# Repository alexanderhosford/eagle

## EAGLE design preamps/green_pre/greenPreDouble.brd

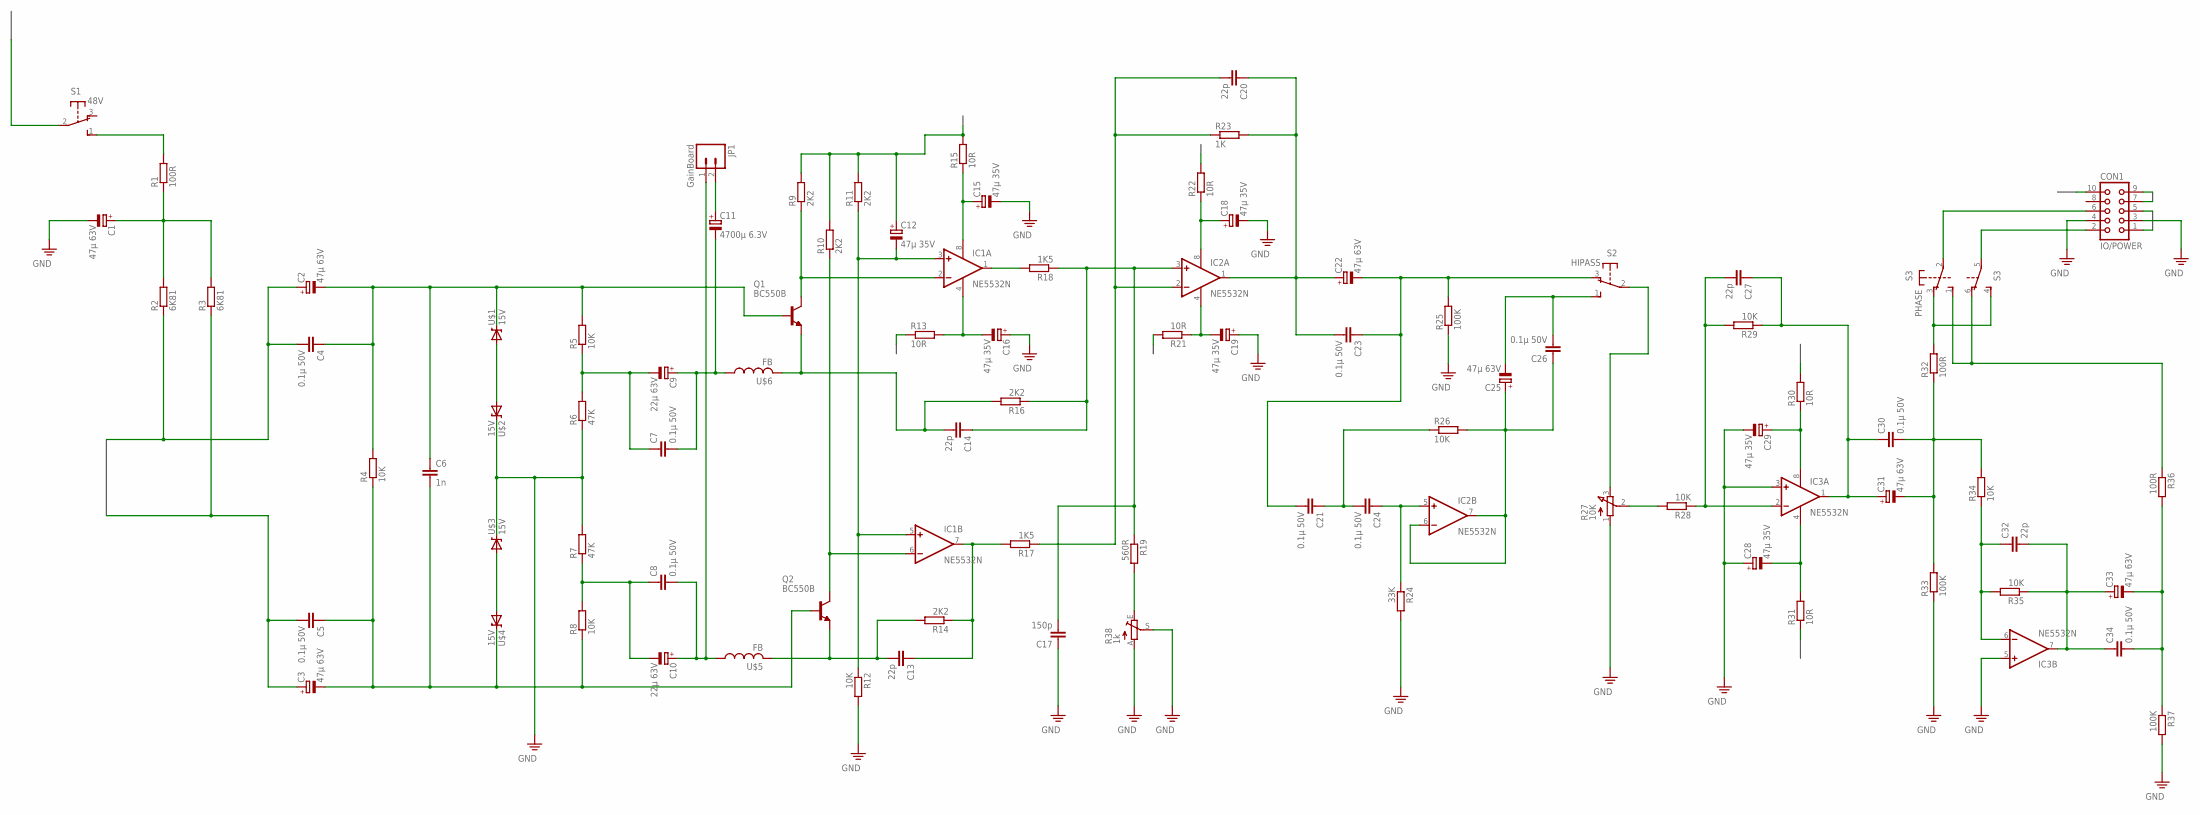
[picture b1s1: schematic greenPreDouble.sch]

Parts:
C1, C2, C3, C22, C25, C31, C33: 47µ 63V; E2,5-5
C4, C5, C7, C8, C21, C23, C24, C26, C30, C34: 0.1µ 50V; C050-025X075
C6: 1n; C050-025X075
C9, C10: 22µ 63V; E2,5-5
C11: 4700µ 6.3V; E2,5-5
C12, C15, C16, C18, C19, C28, C29: 47µ 35V; E2,5-5
C13, C14, C20, C27, C32: 22p; C050-025X075
C17: 150p; C050-025X075
CON1: IO/POWER; CON10
IC1, IC2, IC3: NE5532N; DIL08
JP1: GainBoard; SCREWTERMINAL-3.5MM-2
Q1, Q2: BC550B; TO92-EBC
R1, R32, R36: 100R; 0207/10
R2, R3: 6K81; 0207/10
R4, R5, R8, R12, R26, R28, R29, R34, R35: 10K; 0207/10
R6, R7: 47K; 0207/10
R9, R10, R11, R14, R16: 2K2; 0207/10
R13, R15, R21, R22, R30, R31: 10R; 0207/10
R17, R18: 1K5; 0207/10
R19: 560R; 0207/10
R23: 1K; 0207/10
R24: 33K; 0207/10
R25, R33, R37: 100K; 0207/10
R27: 10K; 3RP/1610N
R38: 1k; B25P
S1: 48V; 9450-1
S2: HIPASS; 9450-1
S3: PHASE; 9450-2
U$1, U$2, U$3, U$4: 15V; DIODE-ZENER
U$5, U$6: FB

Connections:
15V1: C12.+, CON1.9, R9.2, R10.2, R11.2, R15.2, R22.2, R30.2
15V2: CON1.7, R13.1, R21.2, R31.1
48V: CON1.10, S1.2
GND: C1.-, C15.-, C16.+, C17.1, C18.-, C19.+, C28.+, C29.-, CON1.4, IC3.3 (+IN), IC3.5 (+IN), R6.1, R7.2, R12.2, R24.2, R25.1, R27.1 (A), R33.1, R37.2, R38.A, R38.S, U$2.P$1 (C), U$3.P$1 (C)
IN1: C2.+, C4.2, CON1.1, R2.1
IN2: C3.+, C5.2, CON1.5, R3.1
unnamed: C8.2, C10.+, JP1.1, U$5.P$1 (1)
unnamed: IC1.2 (-IN), Q1.C, R9.1
unnamed: C12.-, IC1.3 (+IN), IC1.5 (+IN), R11.1, R12.1
unnamed: IC1.6 (-IN), Q2.C, R10.1
unnamed: C14.2, Q1.E, R16.2, U$6.P$2 (2)
unnamed: C15.+, IC1.8 (V+), R15.1
unnamed: C16.-, IC1.4 (V-), R13.2
unnamed: IC1.1 (OUT), R18.2
unnamed: C7.1, C9.-, R5.1, R6.2
unnamed: C14.1, C17.2, IC2.3 (+IN), R16.1, R18.1, R19.1
unnamed: C7.2, C9.+, C11.-, U$6.P$1 (1)
unnamed: C20.2, IC2.2 (-IN), R17.1, R23.1
unnamed: C8.1, C10.-, R7.1, R8.2
unnamed: U$1.P$2 (A), U$2.P$2 (A)
unnamed: C11.+, JP1.2
unnamed: U$3.P$2 (A), U$4.P$2 (A)
unnamed: C18.+, IC2.8 (V+), R22.1
unnamed: C2.-, C4.1, C6.1, Q1.B, R4.2, R5.2, U$1.P$1 (C)
unnamed: C3.-, C5.1, C6.2, Q2.B, R4.1, R8.1, U$4.P$1 (C)
unnamed: C19.-, IC2.4 (V-), R21.1
unnamed: C20.1, C22.+, C23.2, IC2.1 (OUT), R23.2
unnamed: C21.2, C22.-, C23.1, R25.2, S2.3 (O)
unnamed: C24.1, IC2.5 (+IN), R24.1
unnamed: C13.2, Q2.E, R14.2, U$5.P$2 (2)
unnamed: C13.1, IC1.7 (OUT), R14.1, R17.2
unnamed: C21.1, C24.2, R26.1
unnamed: C25.+, C26.1, IC2.6 (-IN), IC2.7 (OUT), R26.2
unnamed: C25.-, C26.2, S2.1 (S)
unnamed: R27.3 (E), S2.2
unnamed: R19.2, R38.E
unnamed: R1.2, S1.1 (S)
unnamed: C1.+, R1.1, R2.2, R3.2
unnamed: R27.2 (S), R28.2
unnamed: C27.2, IC3.2 (-IN), R28.1, R29.2
unnamed: C27.1, C30.1, C31.+, IC3.1 (OUT), R29.1
unnamed: C28.-, IC3.4 (V-), R31.2
unnamed: C29.+, IC3.8 (V+), R30.1
unnamed: C30.2, C31.-, R32.1, R33.2, R34.2
unnamed: C32.1, IC3.6 (-IN), R34.1, R35.2
unnamed: C32.2, C33.+, C34.1, IC3.7 (OUT), R35.1
unnamed: C33.-, C34.2, R36.2, R37.1
unnamed: R32.2, S3.3 (O), S3.4 (S)
unnamed: R36.1, S3.1 (S), S3.6 (O)
unnamed: CON1.2, S3.5
unnamed: CON1.6, S3.2
PE: CON1.3

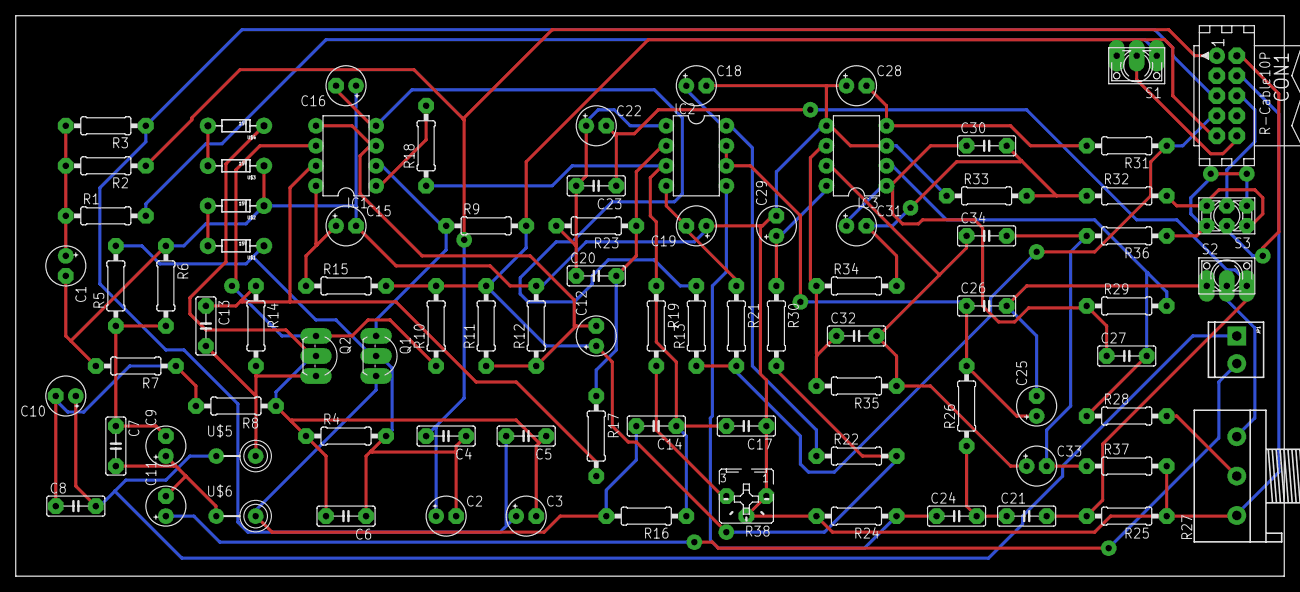
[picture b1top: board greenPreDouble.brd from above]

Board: 2 copper layers, 161.0 x 71.1 mm, 87 parts (0 on the bottom side), 51 nets.

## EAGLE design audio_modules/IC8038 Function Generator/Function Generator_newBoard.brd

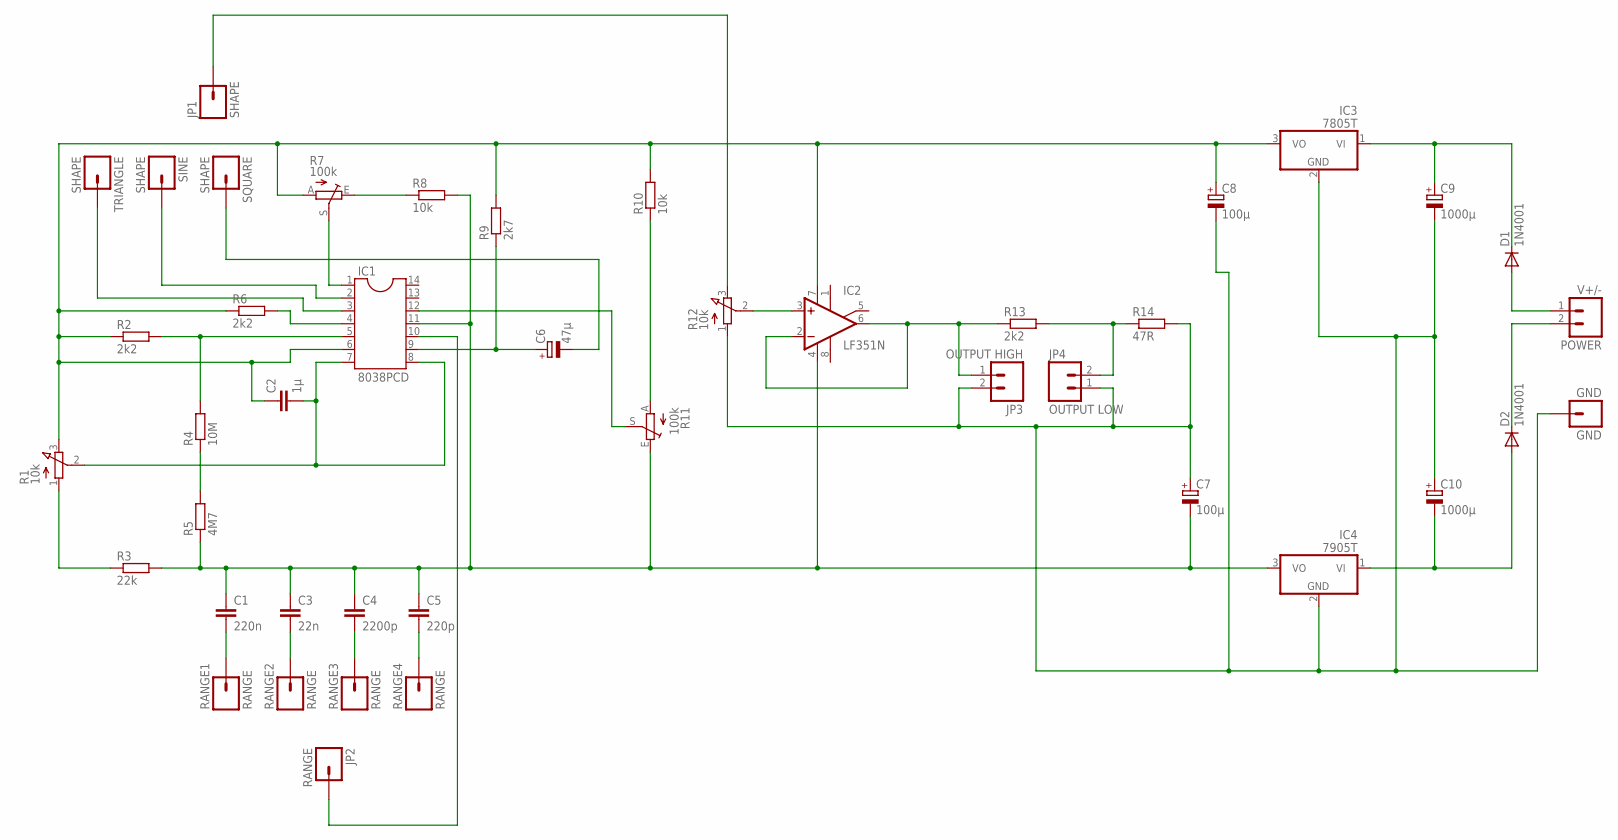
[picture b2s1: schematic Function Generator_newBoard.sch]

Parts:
C1: 220n; C050-035X075
C2: 1µ; C050-035X075
C3: 22n; C050-035X075
C4: 2200p; C050-035X075
C5: 220p; C050-035X075
C6: 47µ; E5-10,5
C7, C8: 100µ; E3,5-8
C9, C10: 1000µ; E5-10,5
D1, D2: 1N4001; DO41-10
GND: GND; 1X01_LONGPAD
IC1: 8038PCD; DIL14
IC2: LF351N; DIL08
IC3: 7805T; TO220H
IC4: 7905T; TO220H
JP1: SHAPE; 1X01_LONGPAD
JP2: RANGE; 1X01_LONGPAD
JP3: OUTPUT HIGH; SCREWTERMINAL-3.5MM-2
JP4: OUTPUT LOW; SCREWTERMINAL-3.5MM-2
POWER: V+/-; SCREWTERMINAL-3.5MM-2
R1, R12: 10k; 3RP/1610N
R2, R6, R13: 2k2; 0207/10
R3: 22k; 0207/10
R4: 10M; 0207/10
R5: 4M7; 0207/10
R7, R11: 100k; S64Y
R8, R10: 10k; 0207/10
R9: 2k7; 0207/10
R14: 47R; 0207/10
RANGE1, RANGE2, RANGE3, RANGE4: RANGE; 1X01_LONGPAD
SINE: SHAPE; 1X01_LONGPAD
SQUARE: SHAPE; 1X01_LONGPAD
TRIANGLE: SHAPE; 1X01_LONGPAD

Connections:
GND: C7.+, C8.-, C9.-, C10.+, GND.1, IC3.2 (GND), IC4.2 (GND), JP3.2, JP4.1, R12.1 (A), R14.2
unnamed: IC1.4 (DUTYCYCLE), R6.2
unnamed: IC1.5 (FREQUENCYADJUST), R2.2, R4.2
unnamed: C2.1, C8.+, IC1.6 (V+), IC2.7 (V+), IC3.3 (VO), R1.3 (E), R2.1, R6.1, R7.A, R9.2, R10.2
unnamed: C2.2, IC1.7 (FMBIAS), IC1.8 (FMSWEEPINPUT), R1.2 (S)
unnamed: R4.1, R5.2
unnamed: C1.1, C3.1, C4.1, C5.1, C7.-, IC1.11 (V-ORGROUND), IC2.4 (V-), IC4.3 (VO), R3.2, R5.1, R8.2, R11.E
unnamed: R1.1 (A), R3.1
unnamed: C3.2, RANGE2.1
unnamed: C4.2, RANGE3.1
unnamed: C1.2, RANGE1.1
unnamed: C5.2, RANGE4.1
unnamed: IC1.10 (TIMINGCAPACITOR), JP2.1
unnamed: C6.+, IC1.9 (SQUAREWAVEOUT), R9.1
unnamed: R7.E, R8.1
unnamed: IC2.2 (-IN), IC2.6 (OUT), JP3.1, R13.1
unnamed: IC1.3 (TRIANGLEOUT), TRIANGLE.1
unnamed: IC1.2 (SINEWAVEOUT), SINE.1
unnamed: IC1.1 (SINEWAVEADJUST), R7.S
unnamed: C6.-, SQUARE.1
unnamed: R10.1, R11.A
unnamed: IC1.12 (SINEWAVEADJUST2), R11.S
unnamed: IC2.3 (+IN), R12.2 (S)
unnamed: JP1.1, R12.3 (E)
unnamed: JP4.2, R13.2, R14.1
unnamed: C10.-, D2.A, IC4.1 (VI)
unnamed: C9.+, D1.C, IC3.1 (VI)
unnamed: D1.A, POWER.1
unnamed: D2.C, POWER.2

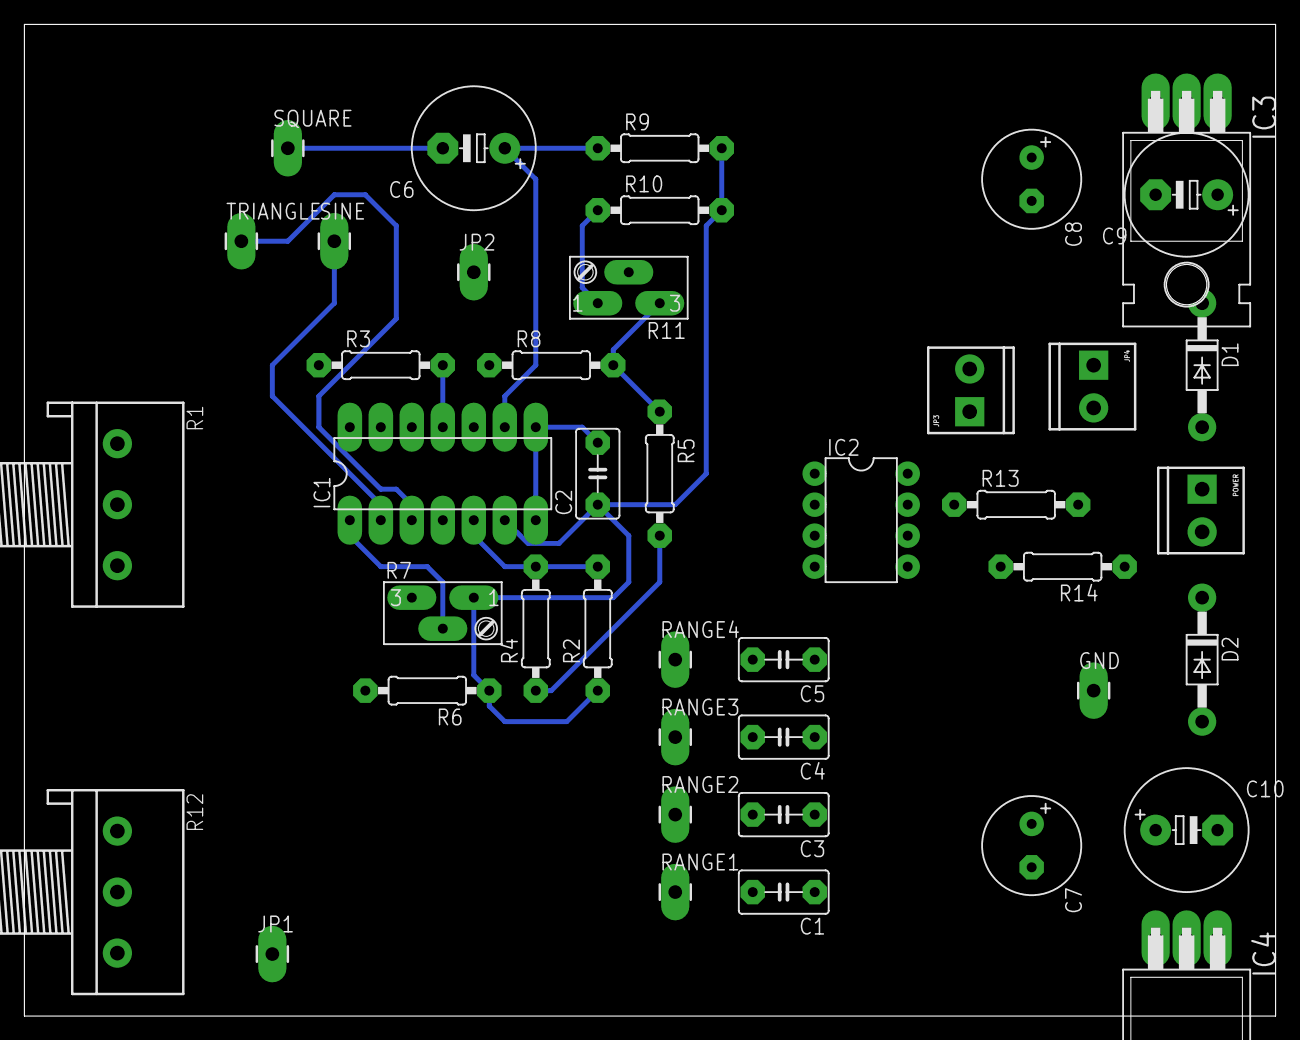
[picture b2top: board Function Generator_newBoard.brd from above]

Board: 2 copper layers, 102.5 x 81.3 mm, 43 parts (0 on the bottom side), 29 nets.

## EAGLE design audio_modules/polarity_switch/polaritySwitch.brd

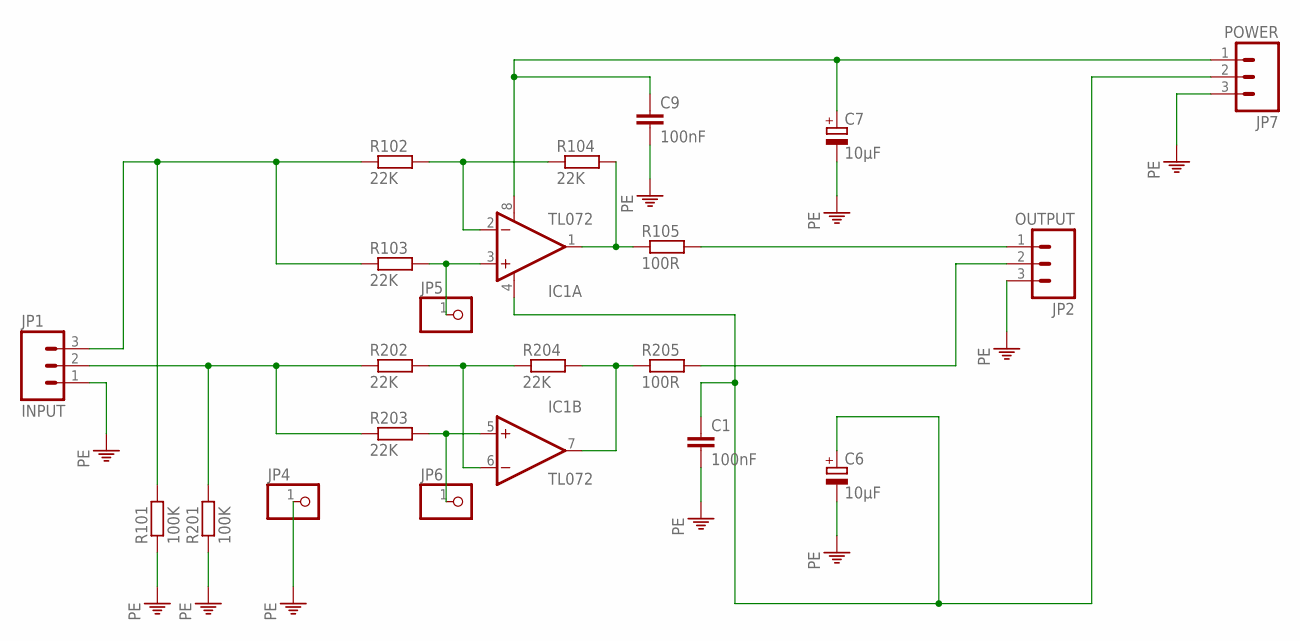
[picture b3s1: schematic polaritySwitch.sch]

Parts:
C1, C9: 100nF; C050-030X075
C6, C7: 10µF; E2,5-6
IC1: TL072; DIP08
JP1: INPUT; SCREWTERMINAL-3.5MM-3
JP2: OUTPUT; SCREWTERMINAL-3.5MM-3
JP4, JP5, JP6: PINHD-1X1; 1X01
JP7: POWER; SCREWTERMINAL-3.5MM-3
R101, R201: 100K; 0207/7
R102, R103, R104, R202, R203, R204: 22K; 0207/7
R105, R205: 100R; 0207/7

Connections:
unnamed: IC1.1 (OUT), R104.2, R105.1
unnamed: IC1.5 (+IN), JP6.1, R203.2
unnamed: JP1.2, R201.2, R202.1, R203.1
unnamed: IC1.3 (+IN), JP5.1, R103.2
unnamed: IC1.7 (OUT), R204.2, R205.1
unnamed: IC1.6 (-IN), R202.2, R204.1
unnamed: JP1.3, R101.2, R102.1, R103.1
unnamed: IC1.2 (-IN), R102.2, R104.1
unnamed: JP2.2, R205.2
unnamed: JP2.1, R105.2
PE: C1.2, C6.-, C7.-, C9.2, JP1.1, JP2.3, JP4.1, JP7.3, R101.1, R201.1
V+: C7.+, C9.1, IC1.8 (V+), JP7.1
V-: C1.1, C6.+, IC1.4 (V-), JP7.2

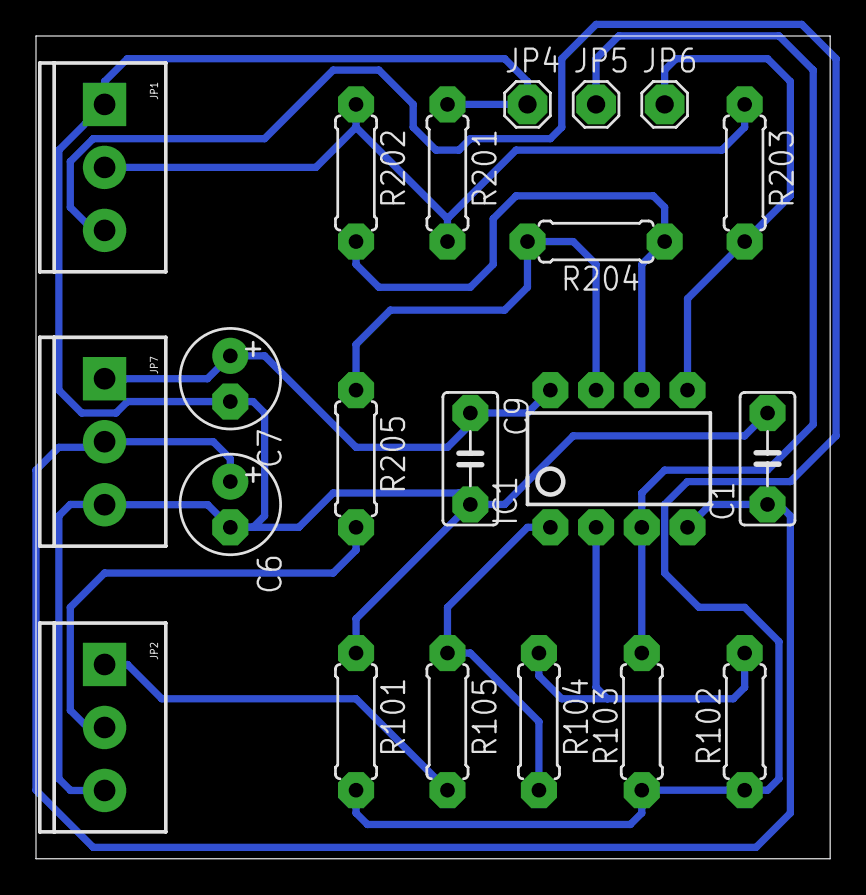
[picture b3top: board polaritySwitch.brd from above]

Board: 2 copper layers, 44.1 x 45.7 mm, 21 parts (0 on the bottom side), 13 nets.

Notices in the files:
parts and their libraries:
SparkFun: Licensing: CC v3.0 Share-Alike You are welcome to use this library for commercial purposes.
